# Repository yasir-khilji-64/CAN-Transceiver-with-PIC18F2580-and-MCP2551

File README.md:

# CAN Transceiver with PIC18F2580 and MCP2551

<h2 align="center"><strong>Developed by Helios LLC</strong></h2>

## Development
Current version is **v2.0**. The device uses **PIC18F25K80** as the base MCU. Other chips include **MCP2551 High-Speed CAN Transceiver**. Board is developed for students who are learning Electronics Design and PCB Design. 

---

## Built With
* [KiCad 5.0](http://kicad.org) - PCB Design Tool

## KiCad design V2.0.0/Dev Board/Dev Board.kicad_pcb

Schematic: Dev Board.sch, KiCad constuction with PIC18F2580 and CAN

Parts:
C1, C2, C3, C5, C10, C12: 100nF; C_1206_3216Metric_Pad1.39x1.80mm_HandSolder; Mfr Part # 12061C104JAT2A
C4, C6: 560pF; C_1206_3216Metric_Pad1.39x1.80mm_HandSolder; Mfr Part # CC1206JKNPOZBN561
C7: 10uF; C_1206_3216Metric_Pad1.39x1.80mm_HandSolder; Mfr Part # CC1206ZRY5V6BB106
C8, C9: 22pF; C_1206_3216Metric_Pad1.39x1.80mm_HandSolder; Mfr Part # 885012008011
C11, C13: 100uF; CP_Elec_5x5.9; Mfr Part # EEE-FT1C101AR
D1: MBR0530; D_SOD-123; Mfr Part # MBR0530
D2, D3, D4, D5, D6, D7, D8, D9: Green; LED_1206_3216Metric_Pad1.22x1.80mm_HandSolder; Mfr Part # HSMG-C150.
J1: PICKIT4 Conn; PinHeader_1x08_P2.54mm_Horizontal; Mfr Part # 61300811021
J2: I2C Conn; PinHeader_1x04_P2.54mm_Vertical; Mfr Part # 61300411121
J3: UART Conn; PinHeader_1x04_P2.54mm_Vertical; Mfr Part # 61300411121
J4: SPI Conn; PinHeader_1x06_P2.54mm_Vertical; Mfr Part # 61300611121
J5: CAN Conn; PinHeader_1x04_P2.54mm_Vertical; Mfr Part # 61300411121
J6: PORT B; PinHeader_1x10_P2.54mm_Vertical
J7: Analog; PinHeader_1x08_P2.54mm_Vertical; Mfr Part # 61300811121
JP1: JP_LED; PinHeader_1x02_P2.54mm_Vertical; Mfr Part # 22-03-2021
R1: 4.7k; R_1206_3216Metric_Pad1.39x1.80mm_HandSolder; Mfr Part # CRS1206-FX-4701ELF
R2: 10k; R_1206_3216Metric_Pad1.39x1.80mm_HandSolder; Mfr Part # TNPW120610K0BEEA
R3, R4: 100; R_1206_3216Metric_Pad1.39x1.80mm_HandSolder; Mfr Part # RC1206FR-07100RL
R5: 1M; R_1206_3216Metric_Pad1.39x1.80mm_HandSolder; Mfr Part # CRCW12061M00FKEA
R6: 330; R_1206_3216Metric_Pad1.39x1.80mm_HandSolder; Mfr Part # RC1206FR-07330RL
TP1: ~MCLR; TestPoint_Pad_D1.0mm
TP2: PGD; TestPoint_Pad_D1.0mm
TP3: PGC; TestPoint_Pad_D1.0mm
TP4: CAN_H; TestPoint_Pad_D1.0mm
TP5: CAN_L; TestPoint_Pad_D1.0mm
TP6: CAN_TXD; TestPoint_Pad_D1.0mm
TP7: CAN_RXD; TestPoint_Pad_D1.0mm
TP8: SCL; TestPoint_Pad_D1.0mm
TP9: SDA; TestPoint_Pad_D1.0mm
TP10: TX1; TestPoint_Pad_D1.0mm
TP11: RX1; TestPoint_Pad_D1.0mm
TP12: SCK; TestPoint_Pad_D1.0mm
TP13: SDI; TestPoint_Pad_D1.0mm
TP14: SDO; TestPoint_Pad_D1.0mm
TP15: ~SS; TestPoint_Pad_D1.0mm
TP16: VCC; TestPoint_Pad_D1.0mm
TP17: GND; TestPoint_Pad_D1.0mm
U1: MCP2551-I-SN; SOIC-8_3.9x4.9mm_P1.27mm; Mfr Part # MCP2551-I/SN
U2: PIC18F25K80_ISS; SSOP-28_5.3x10.2mm_P0.65mm; Mfr Part # PIC18F2580-I/SO
U3: NCP1117-5.0_TO252; TO-252-2; Mfr Part # NCP1117DT50G
Y1: 20MHz; Crystal_SMD_HC49-SD_HandSoldering; Mfr Part # ABLS-20.000MHZ-B2-T

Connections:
+12V: D1.2, J5.1, J7.1
/CAN_H: J5.3, R4.1, TP4.1, U1.7
/CAN_L: J5.4, R3.1, TP5.1, U1.6
/OSC1: C8.1, R5.2, U2.9, Y1.1
/OSC2: C9.1, R5.1, U2.10, Y1.2
/RA0_AN0: J7.8, U2.2
/RA1_AN1: J7.7, U2.3
/RA2_AN2: J7.6, U2.4
/RA3_AN3: J7.5, U2.5
/RA4_AN4: J7.4, U2.7
/RB0: D2.2, J6.3, U2.21
/RB1: D3.2, J6.4, U2.22
/RB2_CANTX: D4.2, J6.5, TP6.1, U1.1, U2.23
/RB3_CANRX: D5.2, J6.6, TP7.1, U1.4, U2.24
/RB4: D6.2, J6.7, U2.25
/RB5: D7.2, J6.8, U2.26
/RB6_PGC: D8.2, J1.4, J6.9, TP3.1, U2.27
/RB7_PGD: D9.2, J1.5, J6.10, TP2.1, U2.28
/RC0: U2.11
/RC1: U2.12
/RX1: J3.4, TP11.1, U2.18
/SCL_SCK: J2.3, J4.5, TP8.1, TP12.1, U2.14
/SDA_SDI: J2.4, J4.4, TP9.1, TP13.1, U2.15
/SDO: J4.3, TP14.1, U2.16
/TX1: J3.3, TP10.1, U2.17
/Vin: C10.1, C11.1, D1.1, U3.3 (VI)
/~MCLR: J1.8, R2.2, TP1.1, U2.1
/~SS: J4.6, TP15.1, U2.13
GND: C1.2, C2.2, C3.2, C4.2, C5.2, C6.2, C7.1, C8.2, C9.2, C10.2, C11.2, C12.2, C13.2, J1.6, J2.2, J3.2, J4.2, J5.2, J6.2, J7.3, JP1.1, R1.2, TP17.1, U1.2, U2.8, U2.19, U3.1 (GND)
unnamed: C4.1, R3.2
unnamed: C6.1, R4.2
unnamed: C7.2, U2.6
unnamed: D2.1, D3.1, D4.1, D5.1, D6.1, D7.1, D8.1, D9.1, R6.1
unnamed: JP1.2, R6.2
unnamed: R1.1, U1.8
VCC: C1.1, C2.1, C3.1, C5.1, C12.1, C13.1, J1.7, J2.1, J3.1, J4.1, J6.1, J7.2, R2.1, TP16.1, U1.3, U2.20, U3.2 (VO)

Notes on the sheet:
CAN Transceiver
PIC18F2580 MCU
Crystal Oscillator
Power
Port B LEDs
RESET and Decoupling Caps
PICKIT4
Test Points
I2C Connector
UART Connector
SPI Connector
CAN Connector
GPIO

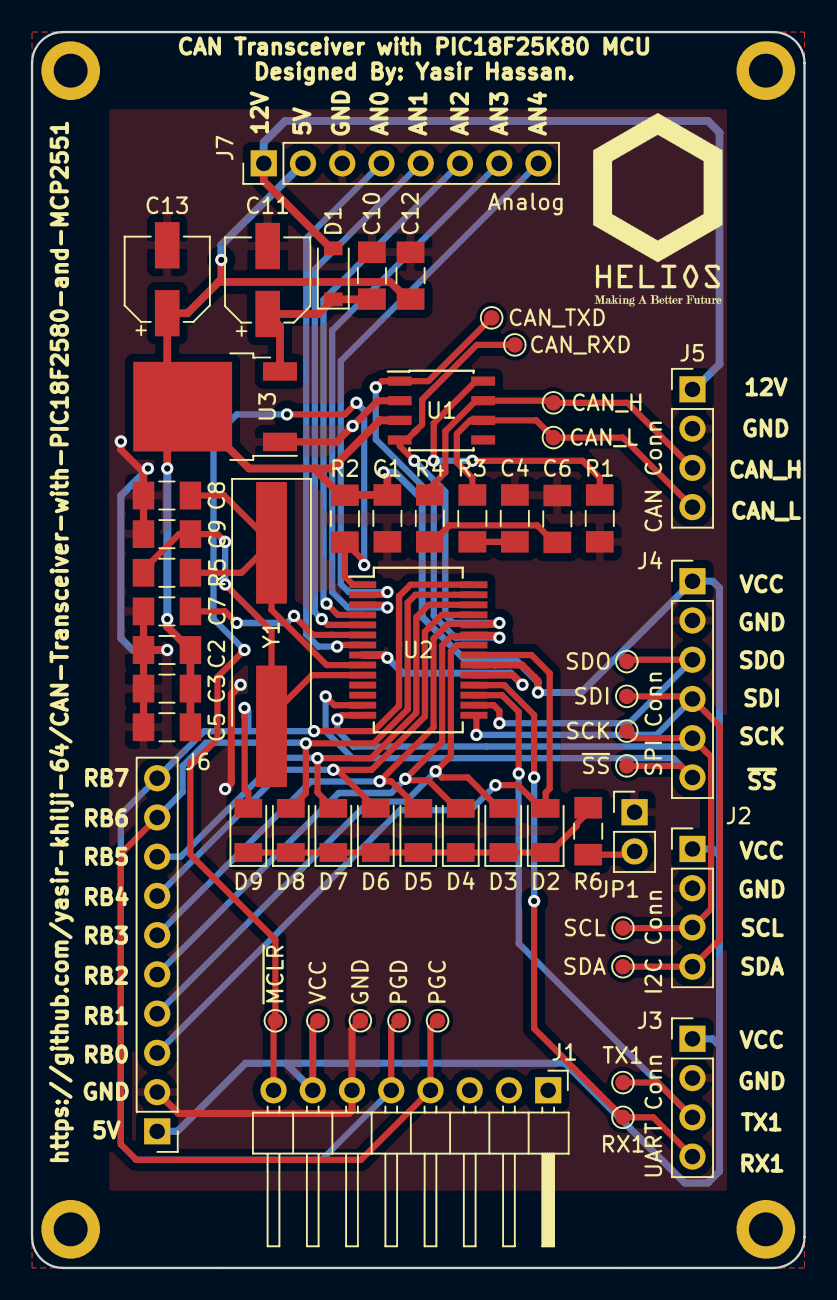
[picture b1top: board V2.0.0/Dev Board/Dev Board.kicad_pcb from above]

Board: 2 copper layers, 50.0 x 80.0 mm, 57 parts (0 on the bottom side), 34 nets.

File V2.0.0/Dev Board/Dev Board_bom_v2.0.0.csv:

Component,Description,Part,References,Value,Footprint,Quantity Per PCB,Datasheet,Supplier-I Part #,Mfr,Mfr Part #,Supplier-I,Nfr Part #
1,Unpolarized capacitor,C,C1 C2 C3 C5 C10 C12,100nF,C_1206_3216Metric_Pad1.39x1.80mm_HandSolder,6,~,2332842,AVX,12061C104JAT2A,Farnell,
2,Polarised capacitor,CP,C11 C13,100uF,CP_Elec_5x5.9,2,~,2065969,Panasonic Electronic Components,EEE-FT1C101AR,Farnell,
3,Unpolarized capacitor,C,C7,10uF,C_1206_3216Metric_Pad1.39x1.80mm_HandSolder,1,~,3188954,Yageo,CC1206ZRY5V6BB106,Farnell,
4,Unpolarized capacitor,C,C8 C9,22pF,C_1206_3216Metric_Pad1.39x1.80mm_HandSolder,2,~,2812188,Wurth Electronics Inc.,885012008011,Farnell,
5,Unpolarized capacitor,C,C4 C6,560pF,C_1206_3216Metric_Pad1.39x1.80mm_HandSolder,2,~,2211027,Yageo,CC1206JKNPOZBN561,Farnell,
6,LED generic,LED,D2 D3 D4 D5 D6 D7 D8 D9,Green,LED_1206_3216Metric_Pad1.22x1.80mm_HandSolder,8,~,8554595,BROADCOM LIMITED,HSMG-C150.,Farnell,
7,Schottky diode,D_Schottky,D1,MBR0530,D_SOD-123,1,~,2463401,ON SEMICONDUCTOR,MBR0530,Farnell,
8,"Generic connector, single row, 01x08, script generated (kicad-library-utils/schlib/autogen/connector/)",Conn_01x08,J7,Analog,PinHeader_1x08_P2.54mm_Vertical,1,~,2356160,WURTH ELEKTRONIK,61300811121,Farnell,
9,"Generic connector, single row, 01x04, script generated (kicad-library-utils/schlib/autogen/connector/)",Conn_01x04,J5,CAN Conn,PinHeader_1x04_P2.54mm_Vertical,1,~,2356155,WURTH ELEKTRONIK,61300411121,Farnell,
10,"Generic connector, single row, 01x04, script generated (kicad-library-utils/schlib/autogen/connector/)",Conn_01x04,J2,I2C Conn,PinHeader_1x04_P2.54mm_Vertical,1,~,2356155,WURTH ELEKTRONIK,61300411121,Farnell,
11,"Generic connector, single row, 01x08, script generated (kicad-library-utils/schlib/autogen/connector/)",Conn_01x08,J1,PICKIT4 Conn,PinHeader_1x08_P2.54mm_Horizontal,1,~,2356183,WURTH ELEKTRONIK,61300811021,Farnell,
12,"Generic connector, single row, 01x10, script generated (kicad-library-utils/schlib/autogen/connector/)",Conn_01x10,J6,PORT B,PinHeader_1x10_P2.54mm_Vertical,1,~,1841229,WURTH ELEKTRONIK,,Farnell,61301011121
13,"Generic connector, single row, 01x06, script generated (kicad-library-utils/schlib/autogen/connector/)",Conn_01x06,J4,SPI Conn,PinHeader_1x06_P2.54mm_Vertical,1,~,2356158,WURTH ELEKTRONIK,61300611121,Farnell,
14,"Generic connector, single row, 01x04, script generated (kicad-library-utils/schlib/autogen/connector/)",Conn_01x04,J3,UART Conn,PinHeader_1x04_P2.54mm_Vertical,1,~,2356155,WURTH ELEKTRONIK,61300411121,Farnell,
15,"Jumper, normally closed",Jumper_NC_Small,JP1,JP_LED,PinHeader_1x02_P2.54mm_Vertical,1,~,9731075,MOLEX,22-03-2021,Farnell,
16,Resistor,R,R3 R4,100,R_1206_3216Metric_Pad1.39x1.80mm_HandSolder,2,~,9240888,Yageo,RC1206FR-07100RL,Farnell,
17,Resistor,R,R2,10k,R_1206_3216Metric_Pad1.39x1.80mm_HandSolder,1,~,1653333,VISHAY,TNPW120610K0BEEA,Farnell,
18,Resistor,R,R5,1M,R_1206_3216Metric_Pad1.39x1.80mm_HandSolder,1,~,1469968,VISHAY,CRCW12061M00FKEA,Farnell,
19,Resistor,R,R6,330,R_1206_3216Metric_Pad1.39x1.80mm_HandSolder,1,~,9240918,Yageo,RC1206FR-07330RL,Farnell,
20,Resistor,R,R1,4.7k,R_1206_3216Metric_Pad1.39x1.80mm_HandSolder,1,~,2470962,Bourns Inc.,CRS1206-FX-4701ELF,Farnell,
21,"High-Speed CAN Transceiver, 1Mbps, 5V supply, SOIC8 package",MCP2551-I-SN,U1,MCP2551-I-SN,SOIC-8_3.9x4.9mm_P1.27mm,1,http://ww1.microchip.com/downloads/en/devicedoc/21667d.pdf,9758569,Microchip Technology,MCP2551-I/SN,Farnell,
22,"1A Low drop-out regulator, Fixed Output 12V, TO-252 (DPAK)",NCP1117-5.0_TO252,U3,NCP1117-5.0_TO252,TO-252-2,1,http://www.onsemi.com/pub_link/Collateral/NCP1117-D.PDF,2296057,ON SEMICONDUCTOR,NCP1117DT50G,Farnell,
23,"32K Flash, 3.5K RAM, 1K EEPROM, PIC18 Microcontroller ADC PWM CAN SPI I2C USART in SSOP28 package",PIC18F25K80_ISS,U2,PIC18F25K80_ISS,SSOP-28_5.3x10.2mm_P0.65mm,1,http://ww1.microchip.com/downloads/en/DeviceDoc/39977f.pdf,9321284,Microchip Technology,PIC18F2580-I/SO,Farnell,
24,Two pin crystal,Crystal,Y1,20MHz,Crystal_SMD_HC49-SD_HandSoldering,1,~,2467724,Abracon LLC,ABLS-20.000MHZ-B2-T,Farnell,





Component Groups:,24
Component Count:,40
Fitted Components:,40
Number of PCBs:,1
Total components:,40
Schematic Version:,v2.0.0
Schematic Date:,2018-10-30
BoM Date:,11/6/2018 1:54:50 AM
Schematic Source:,C:\Personal\Work\Upwork\Raditex Control AB-PIC18F2580 and CAN Work\V2.0.0\Dev Board\Dev Board.sch
KiCad Version:,Eeschema (5.0.0)

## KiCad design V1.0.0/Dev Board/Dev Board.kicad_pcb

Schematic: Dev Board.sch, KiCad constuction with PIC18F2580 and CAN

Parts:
C1, C2, C3, C4, C9, C11: 100nF; C_1206_3216Metric_Pad1.39x1.80mm_HandSolder; Mfr Part # GRM31A5C2J101JW01D
C5, C6: 560pF; C_1206_3216Metric_Pad1.39x1.80mm_HandSolder; Mfr Part # CC1206JKNPOZBN561
C7, C8: 22pF; C_1206_3216Metric_Pad1.39x1.80mm_HandSolder; Mfr Part # 885012008011
C10, C12: 100uF; CP_Elec_5x5.9; Mfr Part # EEE-FT1C101AR
C13: 10uF; C_1206_3216Metric_Pad1.39x1.80mm_HandSolder; Mfr Part # CC1206ZRY5V6BB106
D1, D2, D3: Green; LED_1206_3216Metric_Pad1.22x1.80mm_HandSolder; Mfr Part # LTST-C150GKT
D4: MBR0530; D_SOD-123; Mfr Part # MBR0530
J1: PICKIT4 Conn; PinHeader_1x08_P2.54mm_Vertical; Mfr Part # 61300811121
J2: I2C Conn; PinHeader_1x04_P2.54mm_Vertical; Mfr Part # 61300411121
J3: UART Conn; PinHeader_1x04_P2.54mm_Vertical; Mfr Part # 61300411121
J4: SPI Conn; PinHeader_1x06_P2.54mm_Vertical; Mfr Part # 61300611121
J5: CAN Conn; PinHeader_1x04_P2.54mm_Vertical; Mfr Part # 61300411121
J6: GPIO; PinHeader_1x10_P2.54mm_Vertical; Mfr Part # 61301011121
R1: 4.7k; R_1206_3216Metric_Pad1.39x1.80mm_HandSolder; Mfr Part # CRS1206-FX-4701ELF
R2, R3: 100; R_1206_3216Metric_Pad1.39x1.80mm_HandSolder; Mfr Part # RC1206FR-07100RL
R4: 1M; R_1206_3216Metric_Pad1.39x1.80mm_HandSolder; Mfr Part # AC1206FR-071ML
R5, R6, R7: 330; R_1206_3216Metric_Pad1.39x1.80mm_HandSolder; Mfr Part # RC1206FR-07330RL
R8: 10k; R_1206_3216Metric_Pad1.39x1.80mm_HandSolder; Mfr Part # RT1206BRD0710KL
TP1: ~MCLR~; TestPoint_Pad_D1.0mm
TP2: PGD; TestPoint_Pad_D1.0mm
TP3: PGC; TestPoint_Pad_D1.0mm
TP5: CAN_H; TestPoint_Pad_D1.0mm
TP6: CAN_L; TestPoint_Pad_D1.0mm
TP7: CAN_TXD; TestPoint_Pad_D1.0mm
TP8: CAN_RXD; TestPoint_Pad_D1.0mm
TP9: SCL; TestPoint_Pad_D1.0mm
TP10: SDA; TestPoint_Pad_D1.0mm
TP11: TX1; TestPoint_Pad_D1.0mm
TP12: RX1; TestPoint_Pad_D1.0mm
TP13: SCK; TestPoint_Pad_D1.0mm
TP14: SDI; TestPoint_Pad_D1.0mm
TP15: SDO; TestPoint_Pad_D1.0mm
TP16: ~SS~; TestPoint_Pad_D1.0mm
TP17: VCC; TestPoint_Pad_D1.0mm
TP18: GND; TestPoint_Pad_D1.0mm
U1: MCP2551-I-SN; SOIC-8_3.9x4.9mm_P1.27mm; Mfr Part # MCP2551-I/SN
U2: PIC18F25K80_ISS; SSOP-28_5.3x10.2mm_P0.65mm; Mfr Part # PIC18F2580-I/SO
U3: NCP1117-5.0_TO252; TO-252-2; Mfr Part # NCP1117DT50G
Y1: 20MHz; Crystal_SMD_HC49-SD_HandSoldering; Mfr Part # ABLS-20.000MHZ-B2-T

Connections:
+12V: D4.2, J5.1
/AN0: J6.4, U2.2
/AN1: J6.5, U2.3
/AN2: J6.6, U2.4
/AN3: J6.7, U2.5
/AN4: J6.8, U2.7
/CAN_H: J5.3, R3.1, TP5.1, U1.7
/CAN_L: J5.4, R2.1, TP6.1, U1.6
/CAN_RXD: TP8.1, U1.4, U2.24
/CAN_TXD: TP7.1, U1.1, U2.23
/LED_RB0: D1.2, J6.1, U2.21
/LED_RB1: D2.2, J6.2, U2.22
/LED_RB4: D3.2, J6.3, U2.25
/OSC1: C7.1, R4.2, U2.9, Y1.1
/OSC2: C8.1, R4.1, U2.10, Y1.2
/PGC: J1.5, TP3.1, U2.27
/PGD: J1.4, TP2.1, U2.28
/RX1: J3.4, TP12.1, U2.18
/SCL_SCK: J2.3, J4.3, TP9.1, TP13.1, U2.14
/SDA_SDI: J2.4, J4.4, TP10.1, TP14.1, U2.15
/SDO: J4.5, TP15.1, U2.16
/TX1: J3.3, TP11.1, U2.17
/Vin: C9.1, C10.1, D4.1, U3.3 (VI)
/~MCLR~: J1.1, R8.2, TP1.1, U2.1
/~SS~: J4.6, TP16.1, U2.13
GND: C1.2, C2.2, C3.2, C4.2, C5.2, C6.2, C7.2, C8.2, C9.2, C10.2, C11.2, C12.2, C13.2, J1.3, J2.2, J3.2, J4.2, J5.2, J6.10, R1.2, R5.1, R6.1, R7.1, TP18.1, U1.2, U2.8, U2.19, U3.1 (GND)
unnamed: C5.1, R2.2
unnamed: C6.1, R3.2
unnamed: C13.1, U2.6
unnamed: D1.1, R5.2
unnamed: D2.1, R6.2
unnamed: D3.1, R7.2
unnamed: R1.1, U1.8
VCC: C1.1, C2.1, C3.1, C4.1, C11.1, C12.1, J1.2, J2.1, J3.1, J4.1, J6.9, R8.1, TP17.1, U1.3, U2.20, U3.2 (VO)

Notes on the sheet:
CAN Transceiver
MCU PIC18F2580
Crystal Oscilator
Power
LED Indicators
Decoupling Cap
Reset Pullup
CAN Connector
PICKIT4
I2C
UART
SPI Connector
Test Points
GPIOs

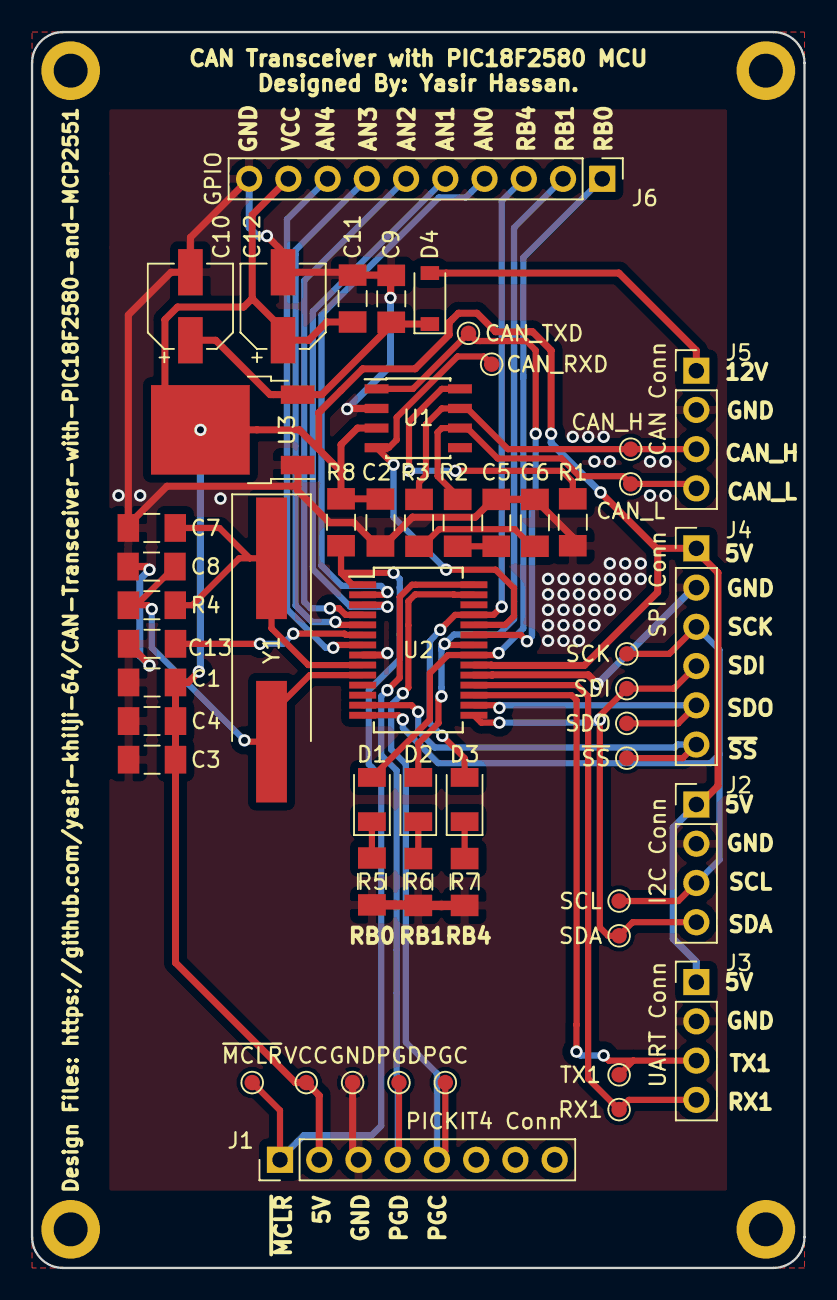
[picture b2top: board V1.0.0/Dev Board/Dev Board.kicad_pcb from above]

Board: 2 copper layers, 50.0 x 80.0 mm, 52 parts (0 on the bottom side), 34 nets.

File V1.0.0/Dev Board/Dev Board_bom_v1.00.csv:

Component,Description,Part,References,Value,Footprint,Quantity Per PCB,Datasheet,Supplier-II Part #,Supplier-I Part #,Supplier-II,Mfr,Mfr Part #,Supplier-I,Supplier-II Price,Supplier-I Price
1,Unpolarized capacitor,C,C1 C2 C3 C4 C9 C11,100nF,C_1206_3216Metric_Pad1.39x1.80mm_HandSolder,6,~,81-GRM31A5C2J101JW01,490-5273-1-ND,Mouser,Murata Electronics North America,GRM31A5C2J101JW01D,Digi-Key,$0.42,$0.42
2,Polarised capacitor,CP,C10 C12,100uF,CP_Elec_5x5.9,2,~,667-EEE-FT1C101AR,P15086CT-ND,Mouser,Panasonic Electronic Components,EEE-FT1C101AR,Digi-Key,$0.55,$0.52
3,Unpolarized capacitor,C,C13,10uF,C_1206_3216Metric_Pad1.39x1.80mm_HandSolder,1,~,603-CC126ZRY5V6BB106,311-2007-1-ND,Mouser,Yageo,CC1206ZRY5V6BB106,Digi-Key,$0.31,$0.32
4,Unpolarized capacitor,C,C7 C8,22pF,C_1206_3216Metric_Pad1.39x1.80mm_HandSolder,2,~,710-885012008011,732-7867-1-ND,Mouser,Wurth Electronics Inc.,885012008011,Digi-Key,$0.11,$0.11
5,Unpolarized capacitor,C,C5 C6,560pF,C_1206_3216Metric_Pad1.39x1.80mm_HandSolder,2,~,603-CC1206JKZBN561,311-4383-1-ND,Mouser,Yageo,CC1206JKNPOZBN561,Digi-Key,$0.26,$0.29
6,LED generic,LED,D1 D2 D3,Green,LED_1206_3216Metric_Pad1.22x1.80mm_HandSolder,3,~,859-LTST-C150GKT,160-1169-1-ND,Mouser,Lite-On Inc.,LTST-C150GKT,Digi-Key,$0.32,$0.34
7,"Schottky diode, small symbol",D_Schottky_Small,D4,MBR0530,D_SOD-123,1,~,512-MBR0530,MBR0530CT-ND,Mouser,ON Semiconductor,MBR0530,Digi-Key,$0.39,$0.40
8,"Generic connector, single row, 01x04, script generated (kicad-library-utils/schlib/autogen/connector/)",Conn_01x04,J5,CAN Conn,PinHeader_1x04_P2.54mm_Vertical,1,~,710-61300411121,732-5317-ND,Mouser,Wurth Electronics Inc.,61300411121,Digi-Key,$0.20,$0.18
9,"Generic connector, single row, 01x10, script generated (kicad-library-utils/schlib/autogen/connector/)",Conn_01x10,J6,GPIO,PinHeader_1x10_P2.54mm_Vertical,1,~,710-61301011121,732-2670-ND,Mouser,Wurth Electronics Inc.,61301011121,Digi-Key,$0.96,$0.89
10,"Generic connector, single row, 01x04, script generated (kicad-library-utils/schlib/autogen/connector/)",Conn_01x04,J2,I2C Conn,PinHeader_1x04_P2.54mm_Vertical,1,~,710-61300411121,732-5317-ND,Mouser,Wurth Electronics Inc.,61300411121,Digi-Key,$0.20,$0.18
11,"Generic connector, single row, 01x08, script generated (kicad-library-utils/schlib/autogen/connector/)",Conn_01x08,J1,PICKIT4 Conn,PinHeader_1x08_P2.54mm_Vertical,1,~,710-61300811121,732-5321-ND,Mouser,Wurth Electronics Inc.,61300811121,Digi-Key,$0.40,$0.37
12,"Generic connector, single row, 01x06, script generated (kicad-library-utils/schlib/autogen/connector/)",Conn_01x06,J4,SPI Conn,PinHeader_1x06_P2.54mm_Vertical,1,~,710-61300611121,732-5319-ND,Mouser,Wurth Electronics Inc.,61300611121,Digi-Key,$0.35,$0.33
13,"Generic connector, single row, 01x04, script generated (kicad-library-utils/schlib/autogen/connector/)",Conn_01x04,J3,UART Conn,PinHeader_1x04_P2.54mm_Vertical,1,~,710-61300411121,732-5317-ND,Mouser,Wurth Electronics Inc.,61300411121,Digi-Key,$0.20,$0.18
14,Resistor,R,R2 R3,100,R_1206_3216Metric_Pad1.39x1.80mm_HandSolder,2,~,603-RC1206FR-07100RL,311-100FRCT-ND,Mouser,Yageo,RC1206FR-07100RL,Digi-Key,$0.23,$0.10
15,Resistor,R,R8,10k,R_1206_3216Metric_Pad1.39x1.80mm_HandSolder,1,~,603-RT1206BRD0710KL,YAG2329CT-ND,Mouser,Yageo,RT1206BRD0710KL,Digi-Key,$0.57,$0.58
16,Resistor,R,R4,1M,R_1206_3216Metric_Pad1.39x1.80mm_HandSolder,1,~,603-AC1206FR-071ML,YAG3832CT-ND,Mouser,Yageo,AC1206FR-071ML,Digi-Key,$0.11,$0.10
17,Resistor,R,R5 R6 R7,330,R_1206_3216Metric_Pad1.39x1.80mm_HandSolder,3,~,603-RC1206FR-07330RL,311-330FRCT-ND,Mouser,Yageo,RC1206FR-07330RL,Digi-Key,$0.23,$0.10
18,Resistor,R,R1,4.7k,R_1206_3216Metric_Pad1.39x1.80mm_HandSolder,1,~,652-CRS1206FX4701ELF,CRS1206-FX-4701ELFCT-ND,Mouser,Bourns Inc.,CRS1206-FX-4701ELF,Digi-Key,$0.36,$0.54
19,"High-Speed CAN Transceiver, 1Mbps, 5V supply, SOIC8 package",MCP2551-I-SN,U1,MCP2551-I-SN,SOIC-8_3.9x4.9mm_P1.27mm,1,http://ww1.microchip.com/downloads/en/devicedoc/21667d.pdf,579-MCP2551-I/SN,MCP2551-I/SN-ND,Mouser,Microchip Technology,MCP2551-I/SN,Digi-Key,$1.06,$1.05
20,"1A Low drop-out regulator, Fixed Output 12V, TO-252 (DPAK)",NCP1117-5.0_TO252,U3,NCP1117-5.0_TO252,TO-252-2,1,http://www.onsemi.com/pub_link/Collateral/NCP1117-D.PDF,863-NCP1117DT50G,NCP1117DT50GOS-ND,Mouser,ON Semiconductor,NCP1117DT50G,Digi-Key,$0.41,$0.41
21,"32K Flash, 3.5K RAM, 1K EEPROM, PIC18 Microcontroller ADC PWM CAN SPI I2C USART in SSOP28 package",PIC18F25K80_ISS,U2,PIC18F25K80_ISS,SSOP-28_5.3x10.2mm_P0.65mm,1,http://ww1.microchip.com/downloads/en/DeviceDoc/39977f.pdf,579-PIC18F2580-I/SO,vPIC18F2580-I/SO-ND,Mouser,Microchip Technology,PIC18F2580-I/SO,Digi-Key,$5.18,$5.16
22,Two pin crystal,Crystal,Y1,20MHz,Crystal_SMD_HC49-SD_HandSoldering,1,~,815-ABLS-20-B2,535-9074-1-ND,Mouser,Abracon LLC,ABLS-20.000MHZ-B2-T,Digi-Key,$0.47,$0.28





Component Groups:,22
Component Count:,35
Fitted Components:,35
Number of PCBs:,1
Total components:,35
Schematic Version:,v1.00
Schematic Date:,2018-09-06
BoM Date:,10/7/2018 4:17:14 PM
Schematic Source:,C:\Personal\Work\Upwork\Raditex Control AB-PIC18F2580 and CAN Work\Dev Board\Dev Board.sch
KiCad Version:,Eeschema (5.0.0)

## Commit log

2018-10-30 v1.0.0
2018-11-05 Version-2.0
2018-11-05 BOM Added
2018-11-17 PGD and PGC Glitch Removed
2021-11-10 Update README.md
    https://forum.kicad.info/t/warning-avoid-all-links-to-kicad-pcb-org-use-kicad-org/31521
